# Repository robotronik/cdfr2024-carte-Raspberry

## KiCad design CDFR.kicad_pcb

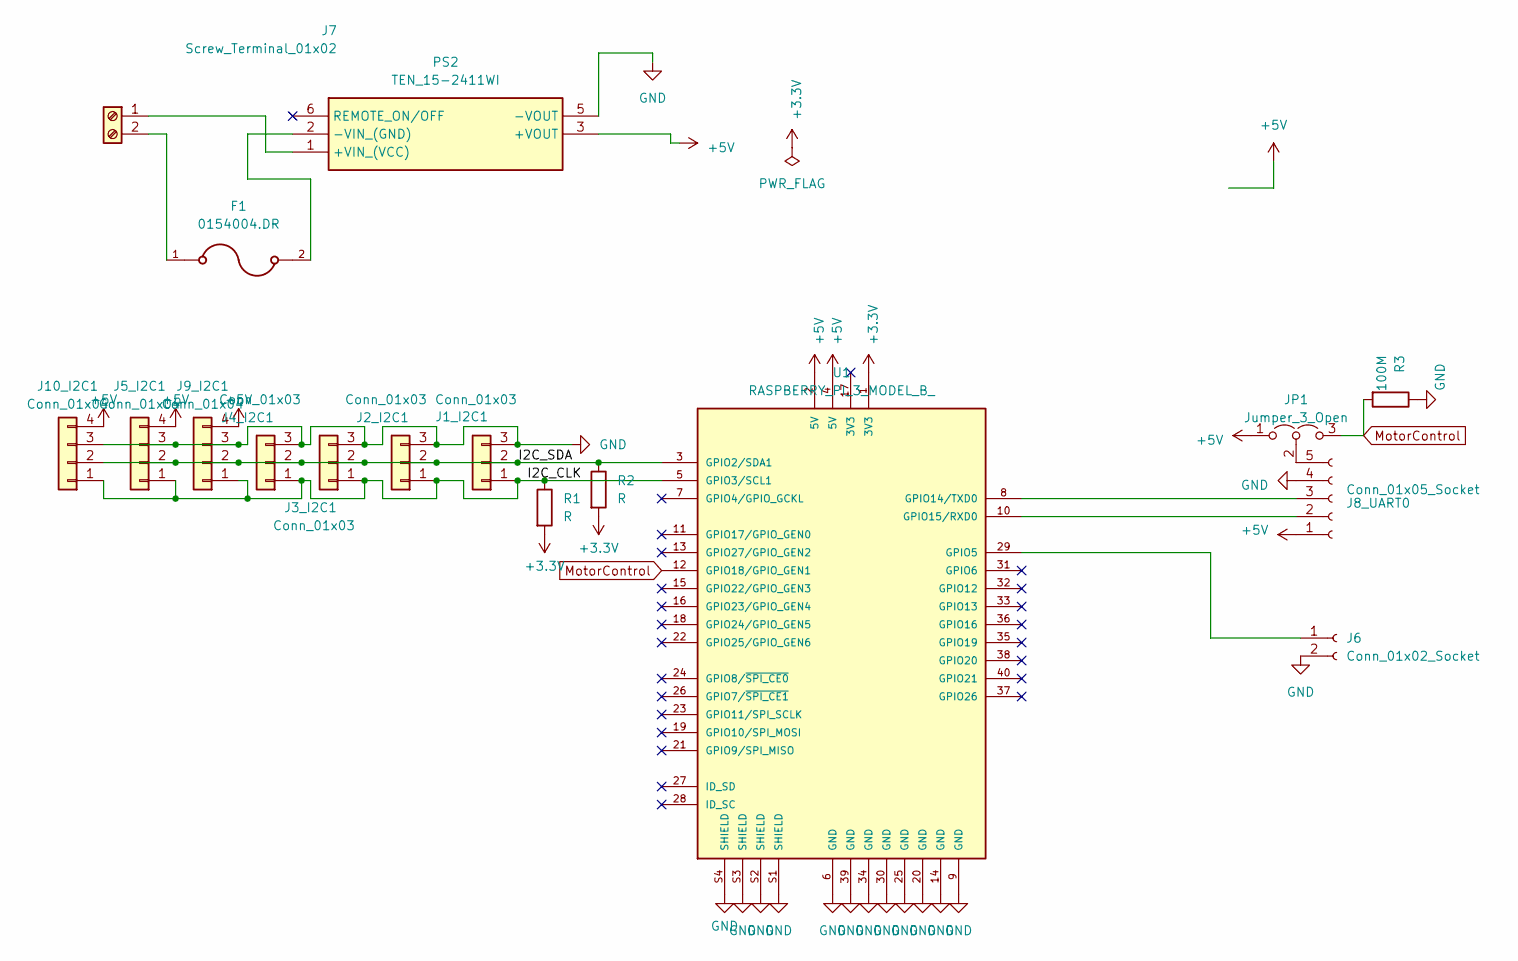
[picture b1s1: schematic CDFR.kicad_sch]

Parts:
F1: 0154004.DR; FUSE_0154004.DR
J1_I2C1, J2_I2C1, J3_I2C1, J4_I2C1: Conn_01x03; JST_XH_B3B-XH-A_1x03_P2.50mm_Vertical
J5_I2C1, J9_I2C1, J10_I2C1: Conn_01x04; JST_XH_B4B-XH-A_1x04_P2.50mm_Vertical
J6: Conn_01x02_Socket; PinHeader_1x02_P2.54mm_Vertical
J7: Screw_Terminal_01x02; CUI_TBP01R1-508-02BE
J8_UART0: Conn_01x05_Socket; JST_XH_B5B-XH-A_1x05_P2.50mm_Vertical
JP1: Jumper_3_Open; PinHeader_1x03_P2.54mm_Vertical
PS2: TEN_15-2411WI; TEN152411WI; Manufacturer_Part_Number TEN 15-2411WI; Mouser Part Number 495-TEN15-2411WI
R1, R2: R; R_0805_2012Metric_Pad1.20x1.40mm_HandSolder
R3: 100M; R_0805_2012Metric
U1: RASPBERRY_PI_3_MODEL_B_; EmpreintPourShiel_RaspberryPi3B; PARTREV N/A

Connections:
+3.3V: R1.2, R2.2, U1.1 (3V3)
+5V: J5_I2C1.4, J8_UART0.1, J9_I2C1.4, J10_I2C1.4, JP1.1 (A), PS2.3 (+VOUT), U1.2 (5V), U1.4 (5V)
/I2C_CLK: J1_I2C1.1, J2_I2C1.1, J3_I2C1.1, J4_I2C1.1, J5_I2C1.1, J9_I2C1.1, J10_I2C1.1, R1.1, U1.5 (GPIO3/SCL1)
/I2C_SDA: J1_I2C1.2, J2_I2C1.2, J3_I2C1.2, J4_I2C1.2, J5_I2C1.2, J9_I2C1.2, J10_I2C1.2, R2.1, U1.3 (GPIO2/SDA1)
GND: J1_I2C1.3, J2_I2C1.3, J3_I2C1.3, J4_I2C1.3, J5_I2C1.3, J6.2, J8_UART0.4, J9_I2C1.3, J10_I2C1.3, PS2.5 (-VOUT), R3.1, U1.6 (GND), U1.9 (GND), U1.14 (GND), U1.20 (GND), U1.25 (GND), U1.30 (GND), U1.34 (GND), U1.39 (GND), U1.S1 (SHIELD), U1.S2 (SHIELD), U1.S3 (SHIELD), U1.S4 (SHIELD); also elsewhere on the board
MotorControl: JP1.3 (B), R3.2, U1.12 (GPIO18/GPIO_GEN1)
unnamed: J6.1, U1.29 (GPIO5)
unnamed 8: J7.1, PS2.1 (+VIN_(VCC)); also elsewhere on the board
unnamed 9: F1.1, J7.2; also elsewhere on the board
unnamed: J8_UART0.2, U1.10 (GPIO15/RXD0)
unnamed: J8_UART0.3, U1.8 (GPIO14/TXD0)
unnamed: J8_UART0.5, JP1.2 (C)
unnamed: F1.2, PS2.2 (-VIN_(GND))

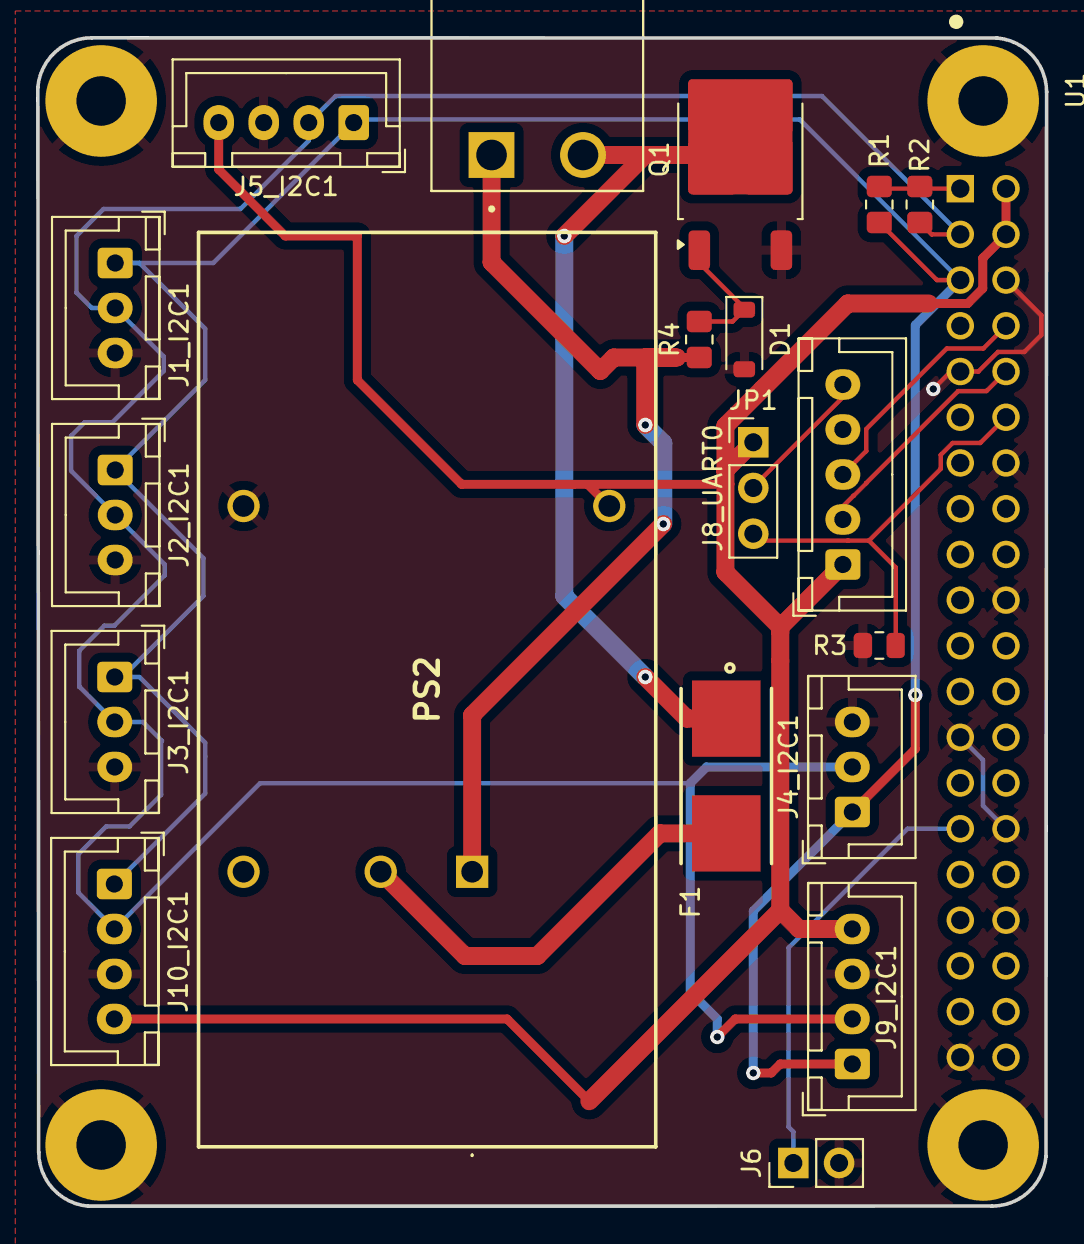
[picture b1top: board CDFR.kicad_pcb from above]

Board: 2 copper layers, 56.0 x 64.9 mm, 20 parts (0 on the bottom side), 14 nets.

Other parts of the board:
D1: D_Zener; D_SOD-123
Q1: Q_NMOS_GDS; TO-252-2
R4: 56k; R_0805_2012Metric_Pad1.20x1.40mm_HandSolder

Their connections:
GND: D1.2 (A), Q1.3 (S); also elsewhere on the board
unnamed: D1.1 (K), Q1.1 (G), R4.2
unnamed 8: R4.1; also elsewhere on the board
unnamed 9: Q1.2 (D); also elsewhere on the board

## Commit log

2024-02-15 ajout lidar et antiRerse voltage
2024-02-29 ajout i2c power
2024-06-14 Mise à jour référence
2024-07-09 TracoPower addition
    Ajout traco power
2024-07-21 Ajout porte fusible
